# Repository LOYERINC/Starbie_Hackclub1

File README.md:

Alright so boom , i tried to make it yesterday but was ahhh spo lets break it down its tarbie but not realy a start
unfportunatly i tried 3d view it didnt work
but all in all it was peak i enjoyed building it , making pcbs although im not good"ive started a course" has been peak ngl "il update readme later" no ai slop today

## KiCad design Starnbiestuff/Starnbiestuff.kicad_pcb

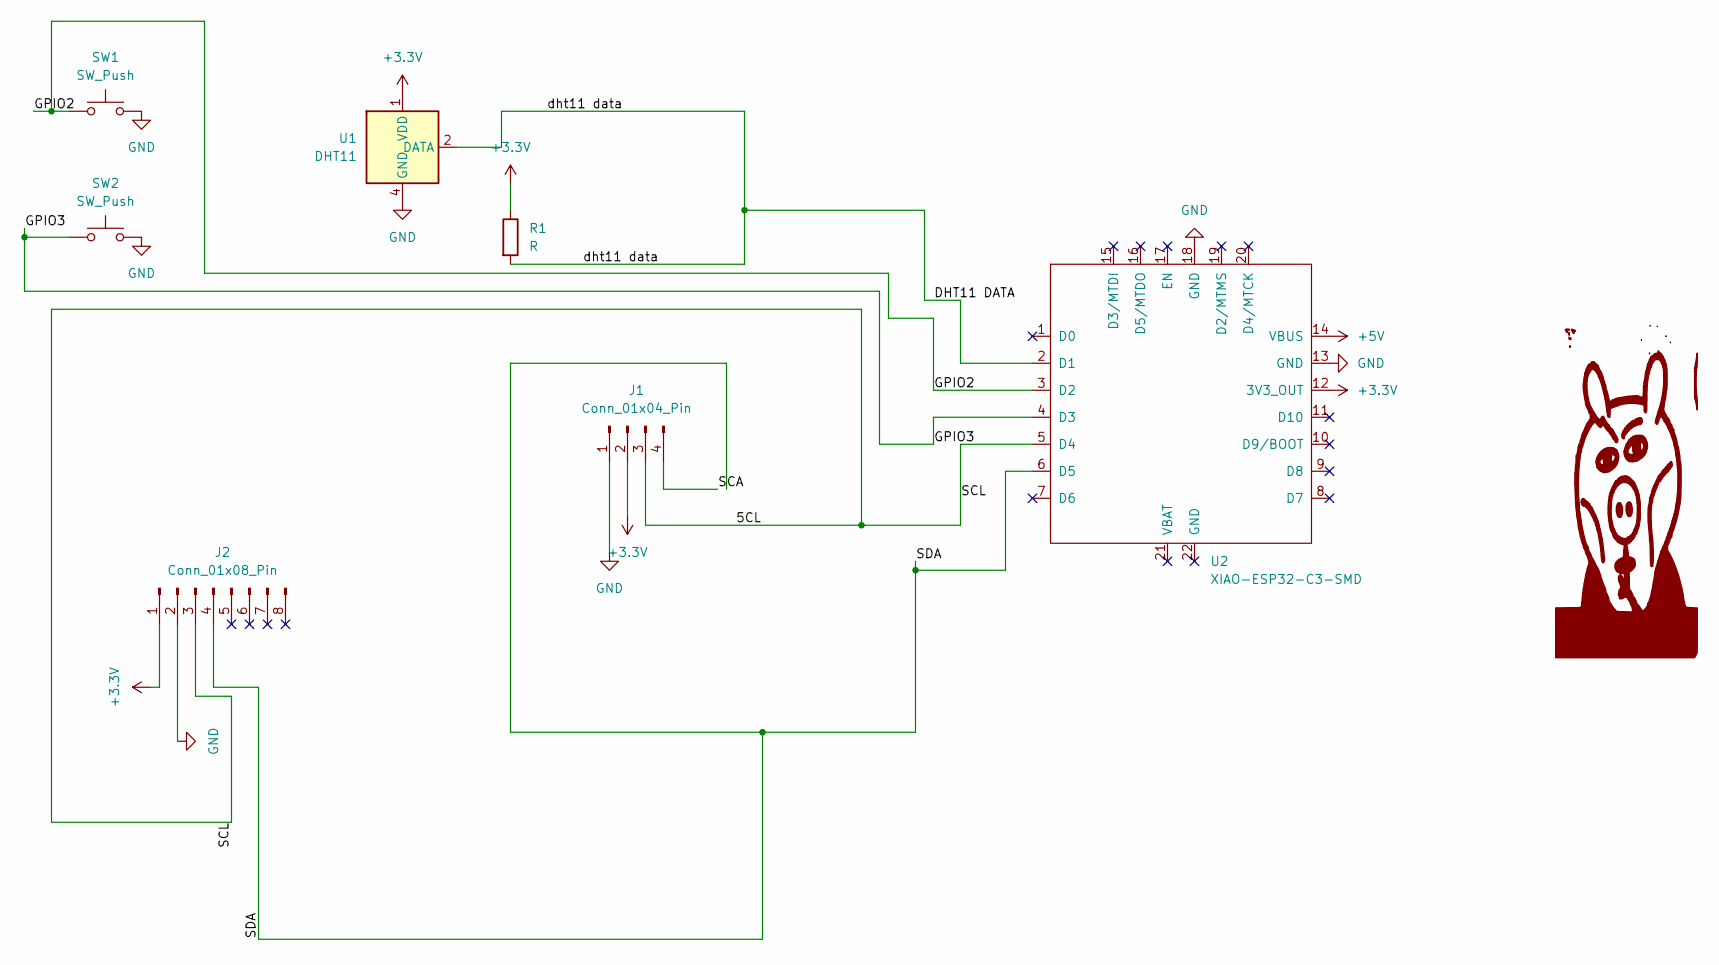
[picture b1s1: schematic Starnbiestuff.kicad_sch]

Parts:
J1: Conn_01x04_Pin; Display_128x64_096_I2C
J2: Conn_01x08_Pin; PinHeader_1x08_P2.54mm_Vertical
R1: R; R_Axial_DIN0204_L3.6mm_D1.6mm_P5.08mm_Horizontal
SW1, SW2: SW_Push; SW_Cherry_MX_1.00u_PCB
U1: DHT11; Aosong_DHT11_5.5x12.0_P2.54mm
U2: XIAO-ESP32-C3-SMD

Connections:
+3.3V: J1.2, J2.1, R1.1, U1.1 (VDD), U2.12 (3V3_OUT)
+5V: U2.14 (VBUS)
/5CL: J1.3, J2.3, U2.5 (D4)
/DHT11 DATA: R1.2, U1.2 (DATA), U2.2 (D1)
/GPIO2: SW1.1, U2.3 (D2)
/GPIO3: SW2.1, U2.4 (D3)
/SCA: J1.4
/SDA: J2.4, U2.6 (D5)
GND: J1.1, J2.2, SW1.2, SW2.2, U1.4 (GND), U2.13 (GND), U2.18 (GND)

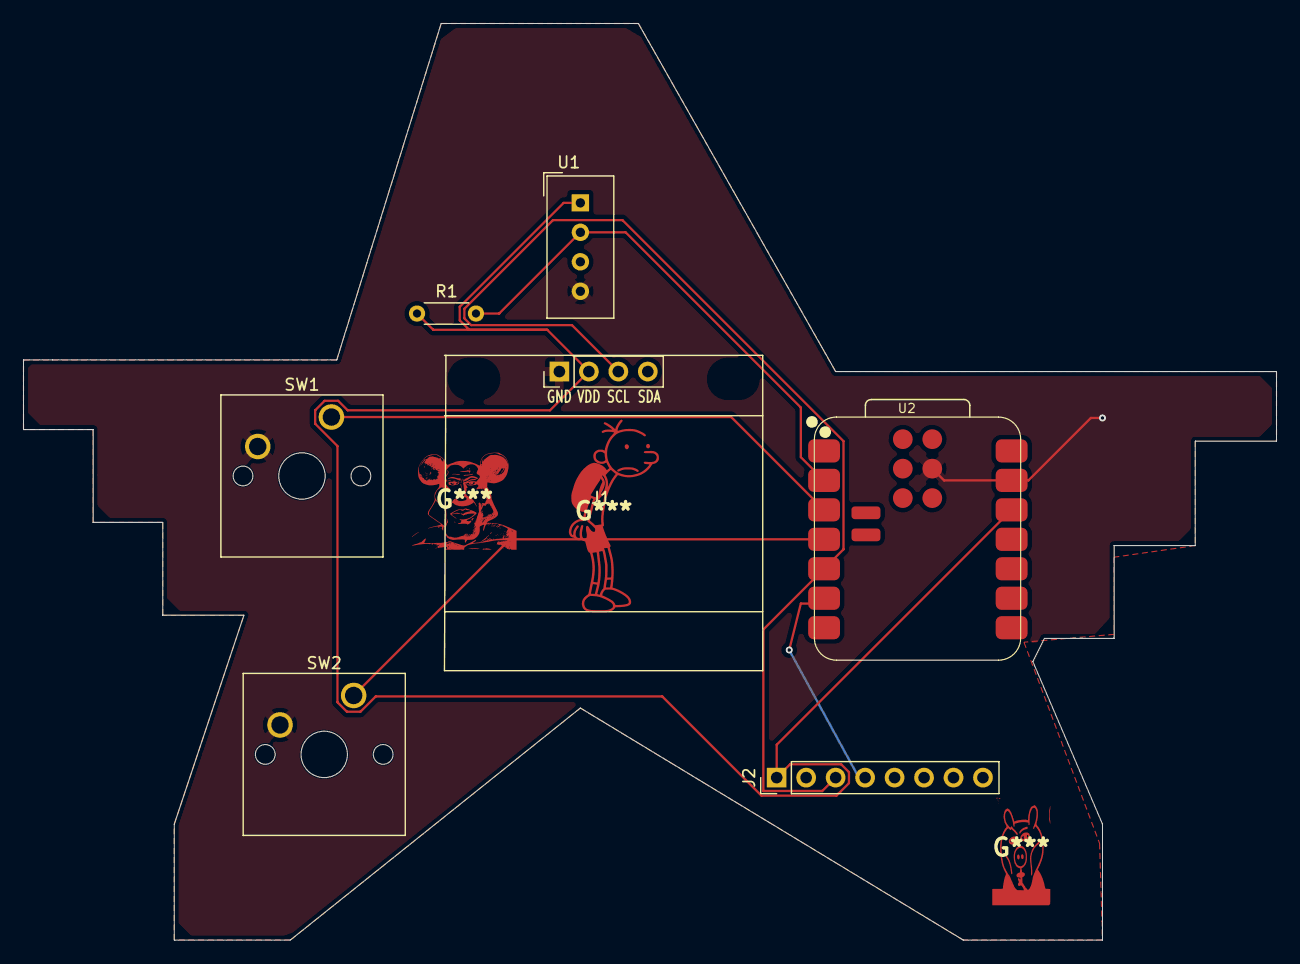
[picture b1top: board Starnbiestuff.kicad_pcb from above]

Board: 2 copper layers, 108.0 x 79.0 mm, 7 parts (0 on the bottom side), 7 nets.
